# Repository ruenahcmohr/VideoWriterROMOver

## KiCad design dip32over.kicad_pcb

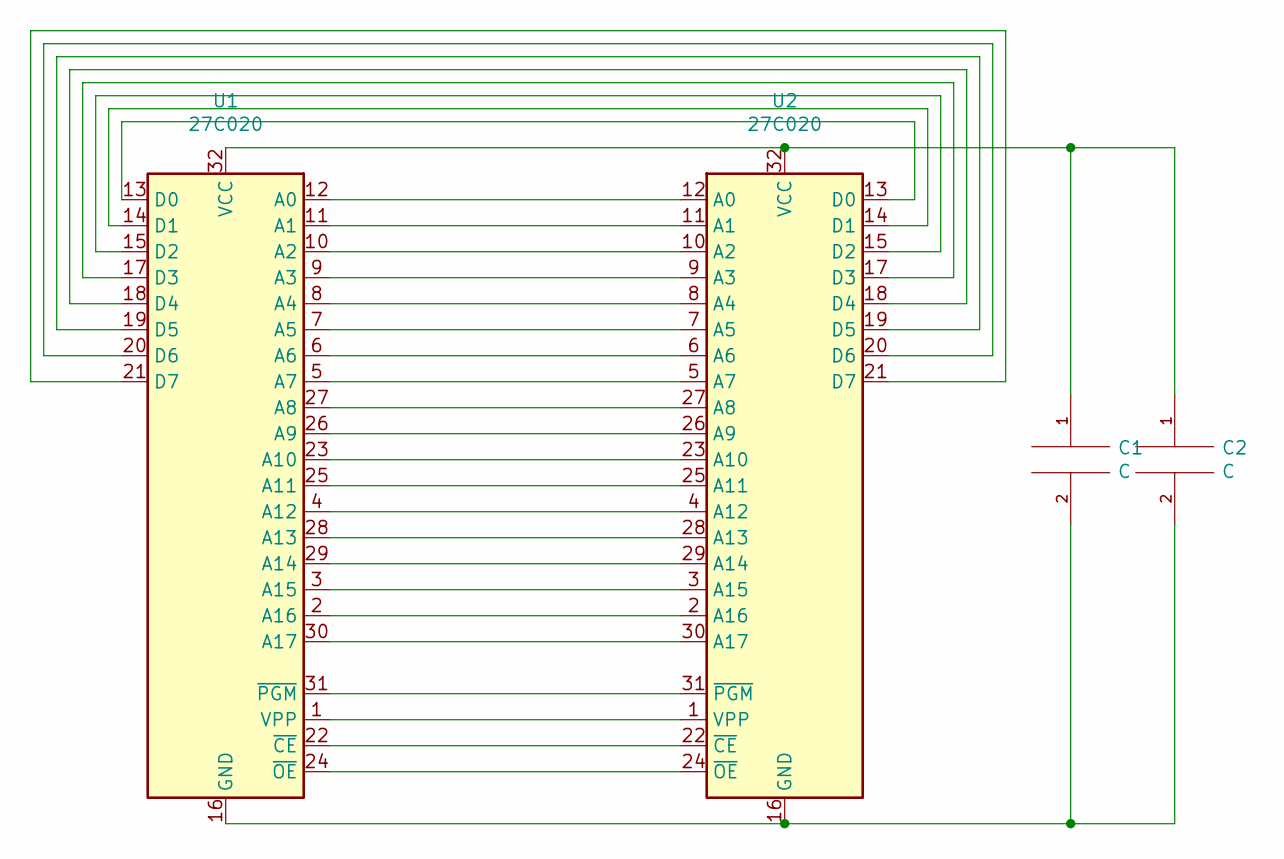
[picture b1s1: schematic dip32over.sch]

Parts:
C1: C; C_0603_1608Metric
C2: C; C_0805_2012Metric
U1, U2: 27C020; DIP-32_W15.24mm_Socket_LongPads

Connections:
unnamed: C1.1, C2.1, U1.32 (VCC), U2.32 (VCC)
unnamed: C1.2, C2.2, U1.16 (GND), U2.16 (GND)
unnamed: U1.1 (VPP), U2.1 (VPP)
unnamed: U1.2 (A16), U2.2 (A16)
unnamed: U1.3 (A15), U2.3 (A15)
unnamed: U1.4 (A12), U2.4 (A12)
unnamed: U1.5 (A7), U2.5 (A7)
unnamed: U1.6 (A6), U2.6 (A6)
unnamed: U1.7 (A5), U2.7 (A5)
unnamed: U1.8 (A4), U2.8 (A4)
unnamed: U1.9 (A3), U2.9 (A3)
unnamed: U1.10 (A2), U2.10 (A2)
unnamed: U1.11 (A1), U2.11 (A1)
unnamed: U1.12 (A0), U2.12 (A0)
unnamed: U1.13 (D0), U2.13 (D0)
unnamed: U1.14 (D1), U2.14 (D1)
unnamed: U1.15 (D2), U2.15 (D2)
unnamed: U1.17 (D3), U2.17 (D3)
unnamed: U1.18 (D4), U2.18 (D4)
unnamed: U1.19 (D5), U2.19 (D5)
unnamed: U1.20 (D6), U2.20 (D6)
unnamed: U1.21 (D7), U2.21 (D7)
unnamed: U1.22 (~CE), U2.22 (~CE)
unnamed: U1.23 (A10), U2.23 (A10)
unnamed: U1.24 (~OE), U2.24 (~OE)
unnamed: U1.25 (A11), U2.25 (A11)
unnamed: U1.26 (A9), U2.26 (A9)
unnamed: U1.27 (A8), U2.27 (A8)
unnamed: U1.28 (A13), U2.28 (A13)
unnamed: U1.29 (A14), U2.29 (A14)
unnamed: U1.30 (A17), U2.30 (A17)
unnamed: U1.31 (~PGM), U2.31 (~PGM)

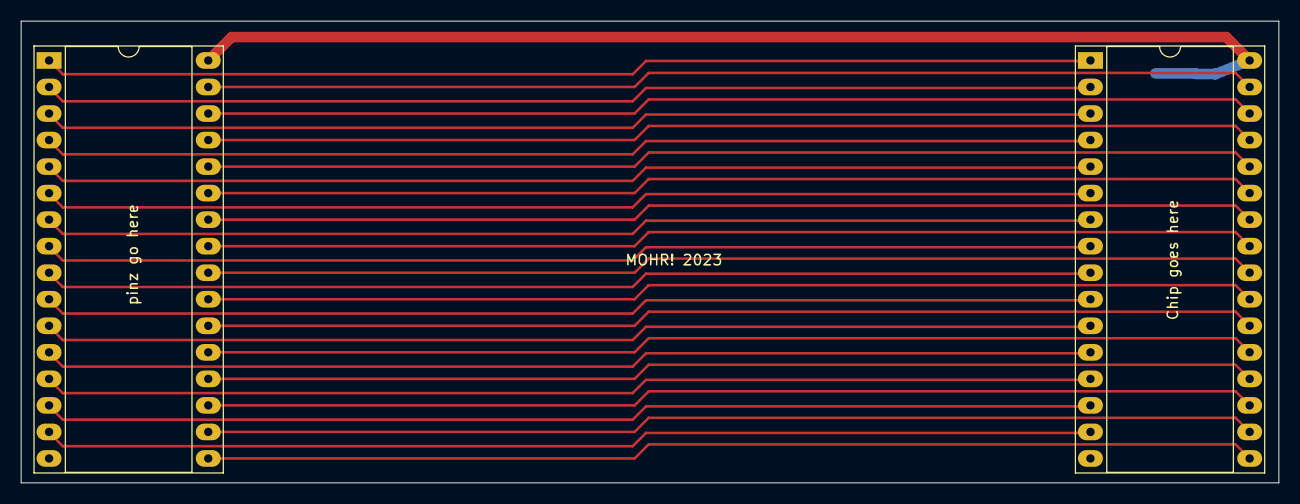
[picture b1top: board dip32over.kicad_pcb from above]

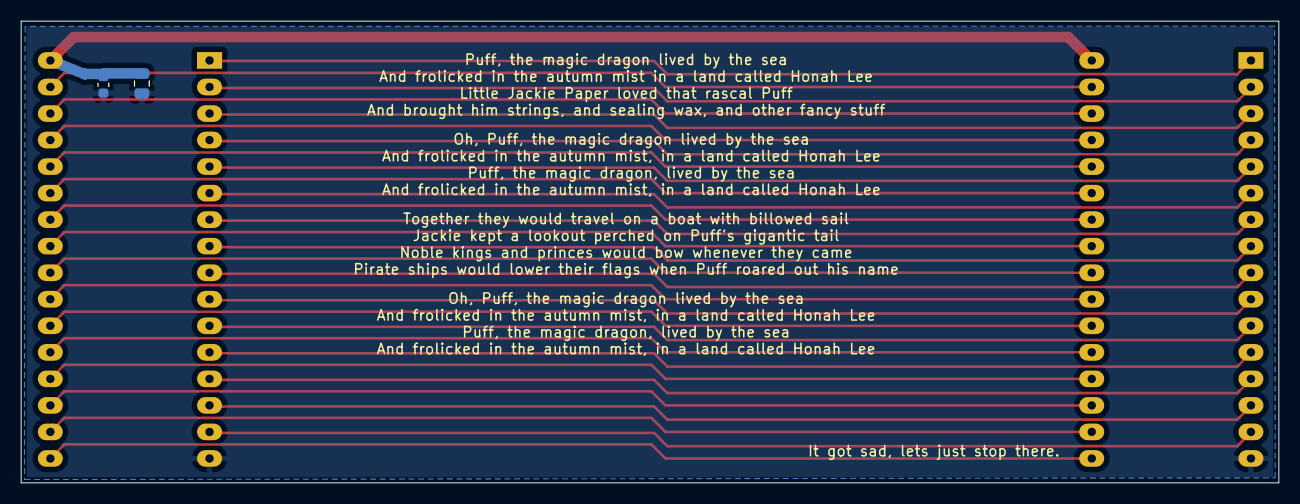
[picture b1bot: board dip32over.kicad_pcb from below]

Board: 2 copper layers, 120.4 x 44.2 mm, 4 parts (2 on the bottom side), 32 nets.

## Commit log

2023-03-01 adding files
